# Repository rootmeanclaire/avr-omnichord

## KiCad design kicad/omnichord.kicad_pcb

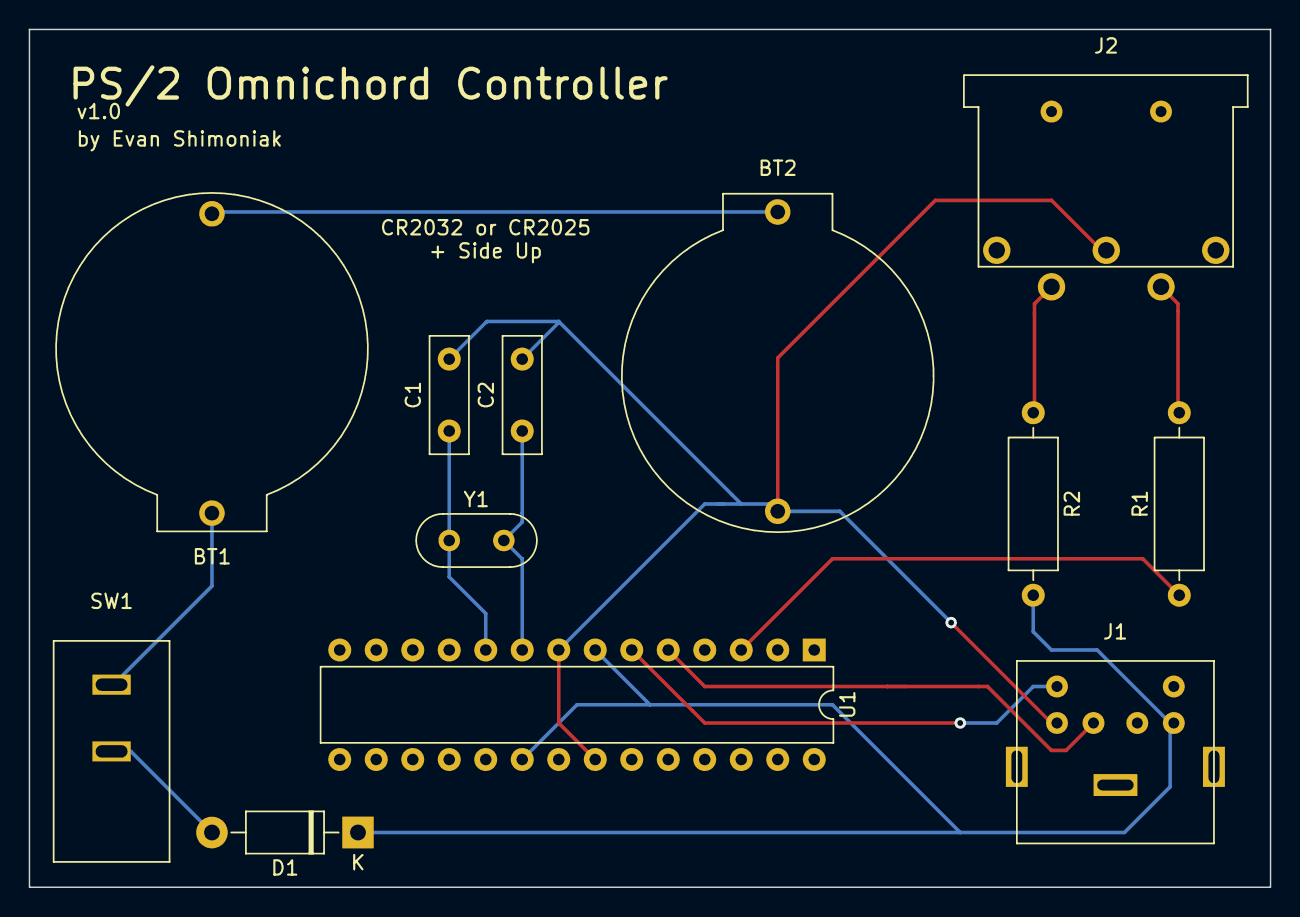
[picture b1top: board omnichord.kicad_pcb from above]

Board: 2 copper layers, 86.4 x 59.7 mm, 12 parts (0 on the bottom side), 12 nets.

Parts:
BT1, BT2: Battery_Cell; Battery-Holder_CR2025-CR2032
C1, C2: 20p; C_Disc_D8.0mm_W2.5mm_P5.00mm
D1: 1N4001; D_DO-41_SOD81_P10.16mm_Horizontal
J1: Mini-DIN-6; MINI-DIN-6
J2: DIN-5_180degree; MIDI_DIN5
R1, R2: 220; R_Axial_DIN0309_L9.0mm_D3.2mm_P12.70mm_Horizontal
SW1: SW_SPST; SW_AMZN_001
U1: ATmega328P-PU; DIP-28_W7.62mm
Y1: Crystal; Crystal_HC52-U_Vertical

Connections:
/GND: BT2.2, C1.2, C2.2, J1.3, J2.2, U1.8, U1.22
/PD3: J1.1, U1.5
/PD4: J1.5, U1.6
/TX: R1.1, U1.3
/VCC: D1.1, J1.4, R2.2, U1.7, U1.20
/XTAL1: C2.1, U1.9, Y1.2
/XTAL2: C1.1, U1.10, Y1.1
unnamed: BT1.1, SW1.1
unnamed: BT1.2, BT2.1
unnamed: D1.2, SW1.2
unnamed: J2.4, R2.1
unnamed: J2.5, R1.2

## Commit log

2020-06-11 MIDI Output Test
2020-06-11 Chord loop test
2020-06-20 Single key input
2020-06-20 Single key chord qualities
2020-06-20 Removed debug LED
2020-06-20 Added missing end keys
2020-06-20 Added LICENSE (GPL v3)
2022-11-15 Added original PCB design files
